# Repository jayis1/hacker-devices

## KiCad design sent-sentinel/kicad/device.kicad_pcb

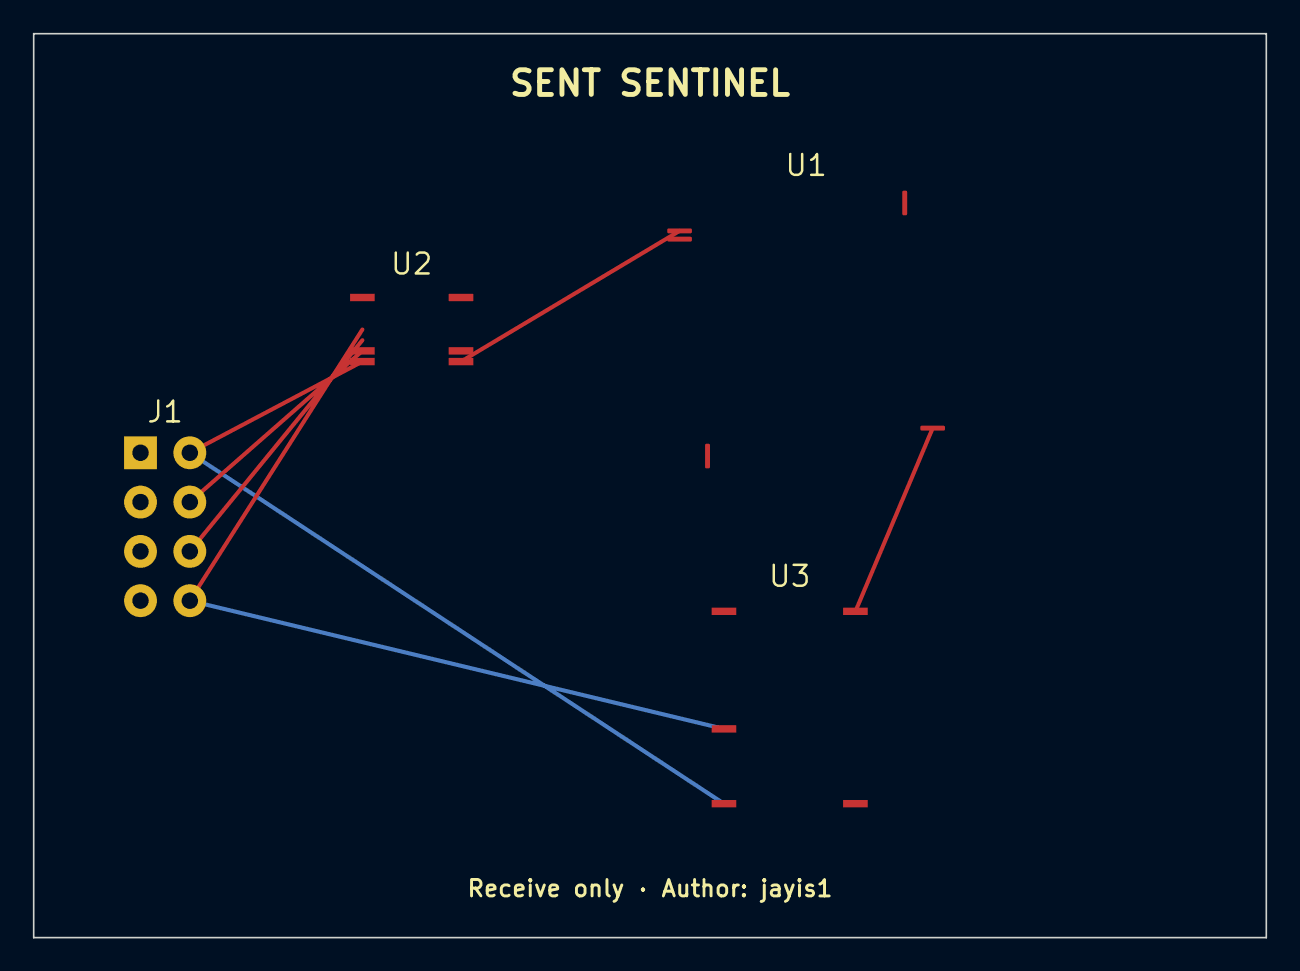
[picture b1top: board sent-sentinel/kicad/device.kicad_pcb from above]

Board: 2 copper layers, 75.0 x 55.0 mm, 4 parts (0 on the bottom side), 7 nets.

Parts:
J1: SENT_AND_ANALOG; Molex_Micro-Fit_3.0_43045-0800_2x04_P3.00mm_Horizontal
U1: STM32G474VET6; LQFP-100_14x14mm_P0.5mm
U2: 74LVC14A; TSSOP-14_4.4x5mm_P0.65mm
U3: ADS8684IDBTR; TSSOP-38_6.1x12.5mm_P0.65mm

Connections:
+3V3: U1.100, U2.14, U3.38
ADC_SPI: U1.50, U3.20
ANALOG_CH0: J1.2, U3.1
ANALOG_CH3: J1.8, U3.8
GND: U1.75, U2.7, U3.19
SENT_CH0_RX: J1.1, U1.1, U2.1, U2.2
SENT_CH1_RX: J1.3, U2.3, U2.4

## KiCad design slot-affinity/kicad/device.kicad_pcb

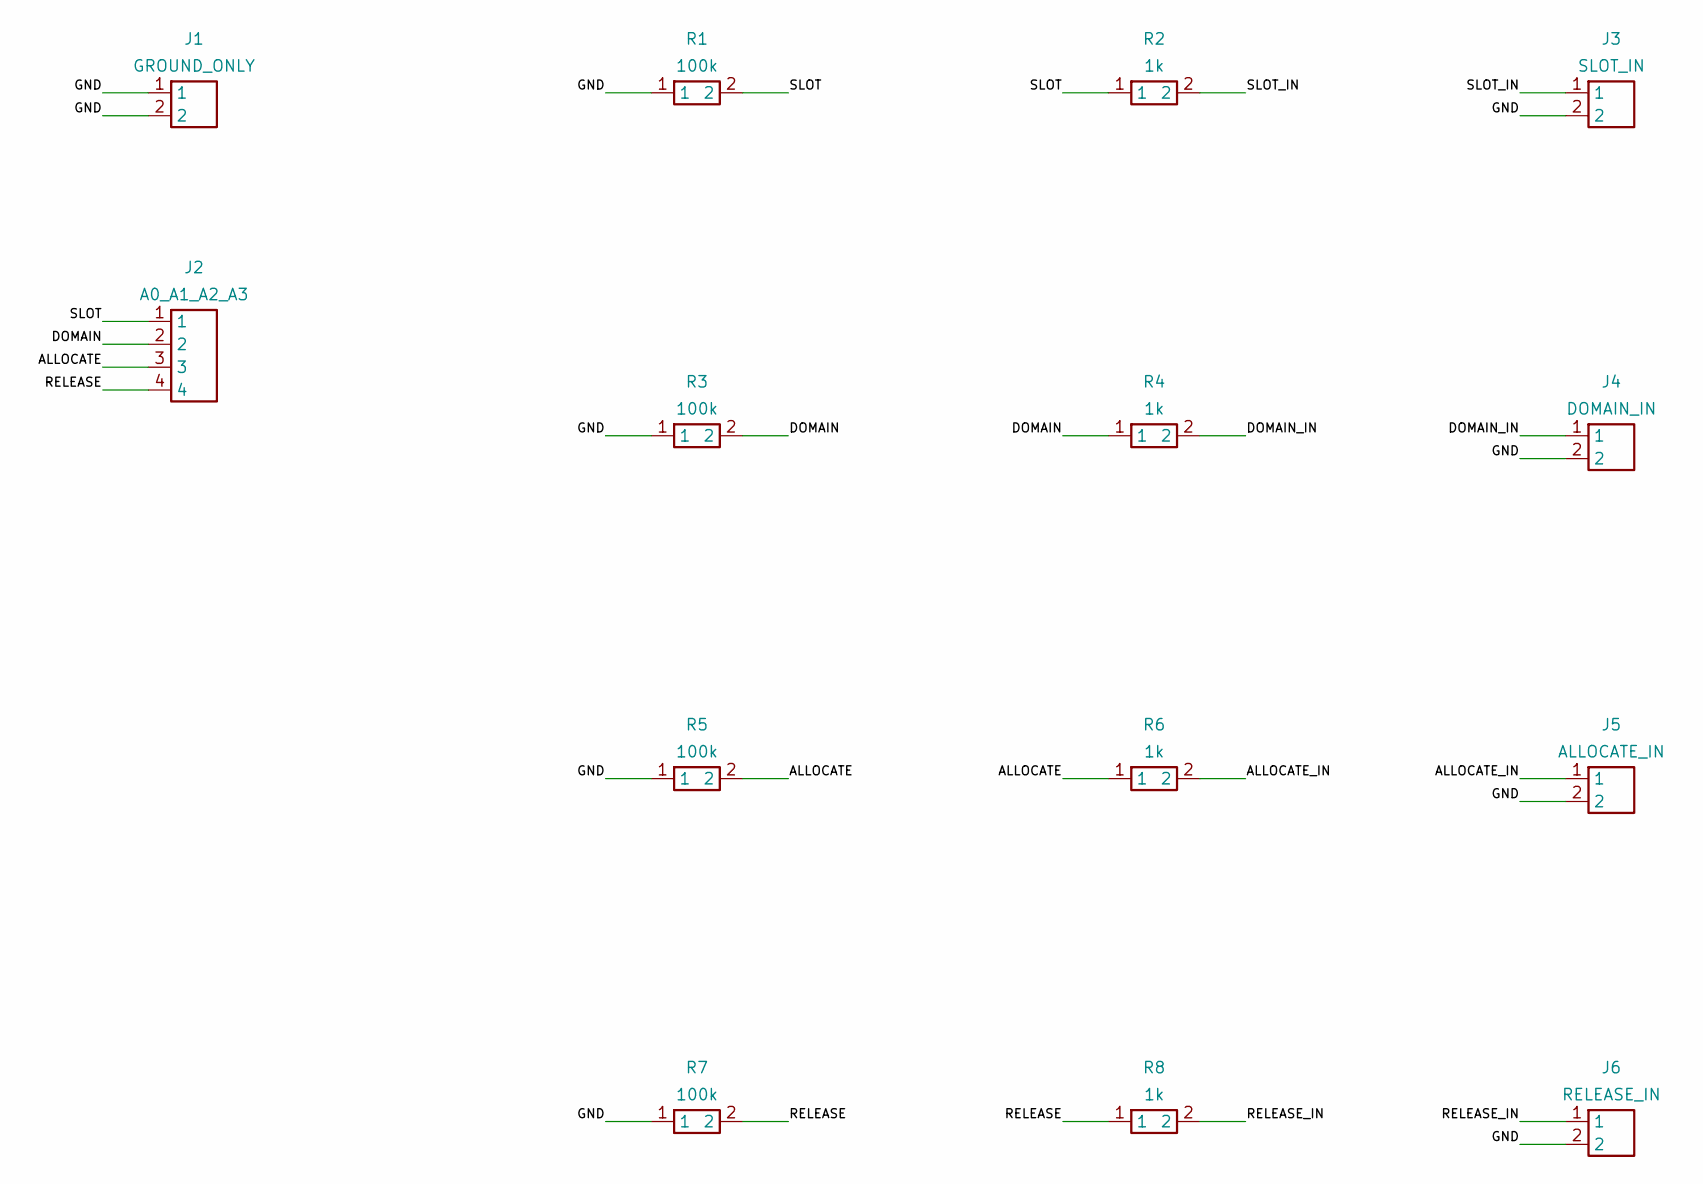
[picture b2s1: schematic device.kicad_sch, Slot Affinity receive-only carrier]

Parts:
J1: GROUND_ONLY; PinHeader_1x02_P2.54mm_Vertical
J2: A0_A1_A2_A3; PinHeader_1x04_P2.54mm_Vertical
J3: SLOT_IN; PinHeader_1x02_P2.54mm_Vertical
J4: DOMAIN_IN; PinHeader_1x02_P2.54mm_Vertical
J5: ALLOCATE_IN; PinHeader_1x02_P2.54mm_Vertical
J6: RELEASE_IN; PinHeader_1x02_P2.54mm_Vertical
R1, R3, R5, R7: 100k; R_Axial_DIN0207_L6.3mm_D2.5mm_P7.62mm_Horizontal
R2, R4, R6, R8: 1k; R_Axial_DIN0207_L6.3mm_D2.5mm_P7.62mm_Horizontal

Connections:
ALLOCATE: J2.3, R5.2, R6.1
ALLOCATE_IN: J5.1, R6.2
DOMAIN: J2.2, R3.2, R4.1
DOMAIN_IN: J4.1, R4.2
GND: J1.1, J1.2, J3.2, J4.2, J5.2, J6.2, R1.1, R3.1, R5.1, R7.1
RELEASE: J2.4, R7.2, R8.1
RELEASE_IN: J6.1, R8.2
SLOT: J2.1, R1.2, R2.1
SLOT_IN: J3.1, R2.2

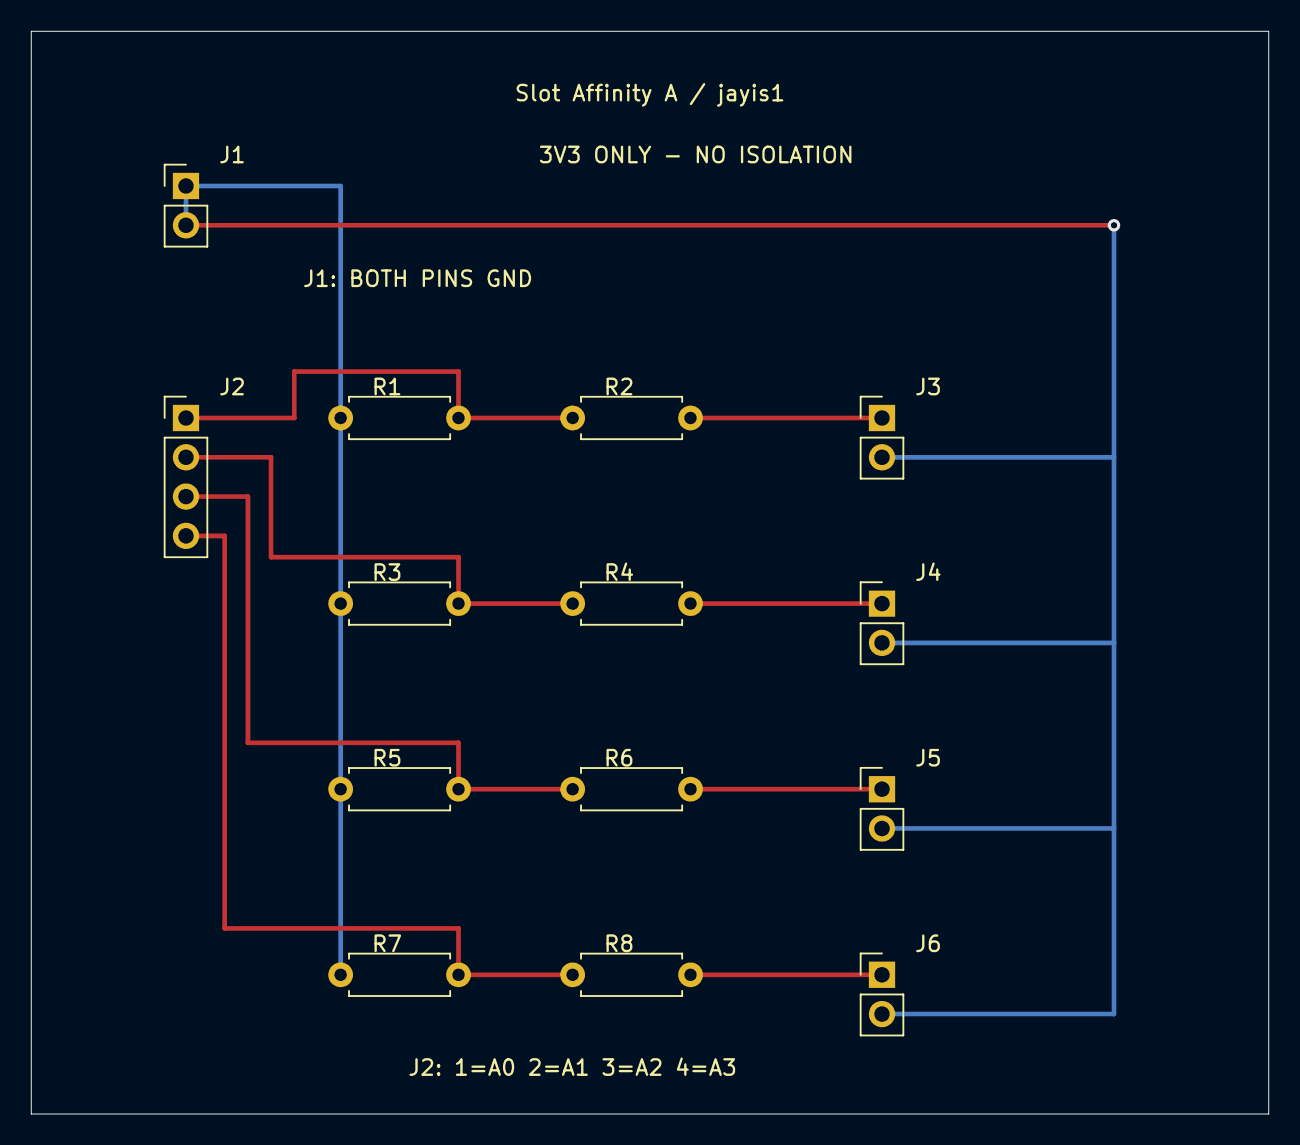
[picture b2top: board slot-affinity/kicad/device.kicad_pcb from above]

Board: 2 copper layers, 80.0 x 70.0 mm, 14 parts (0 on the bottom side), 9 nets.

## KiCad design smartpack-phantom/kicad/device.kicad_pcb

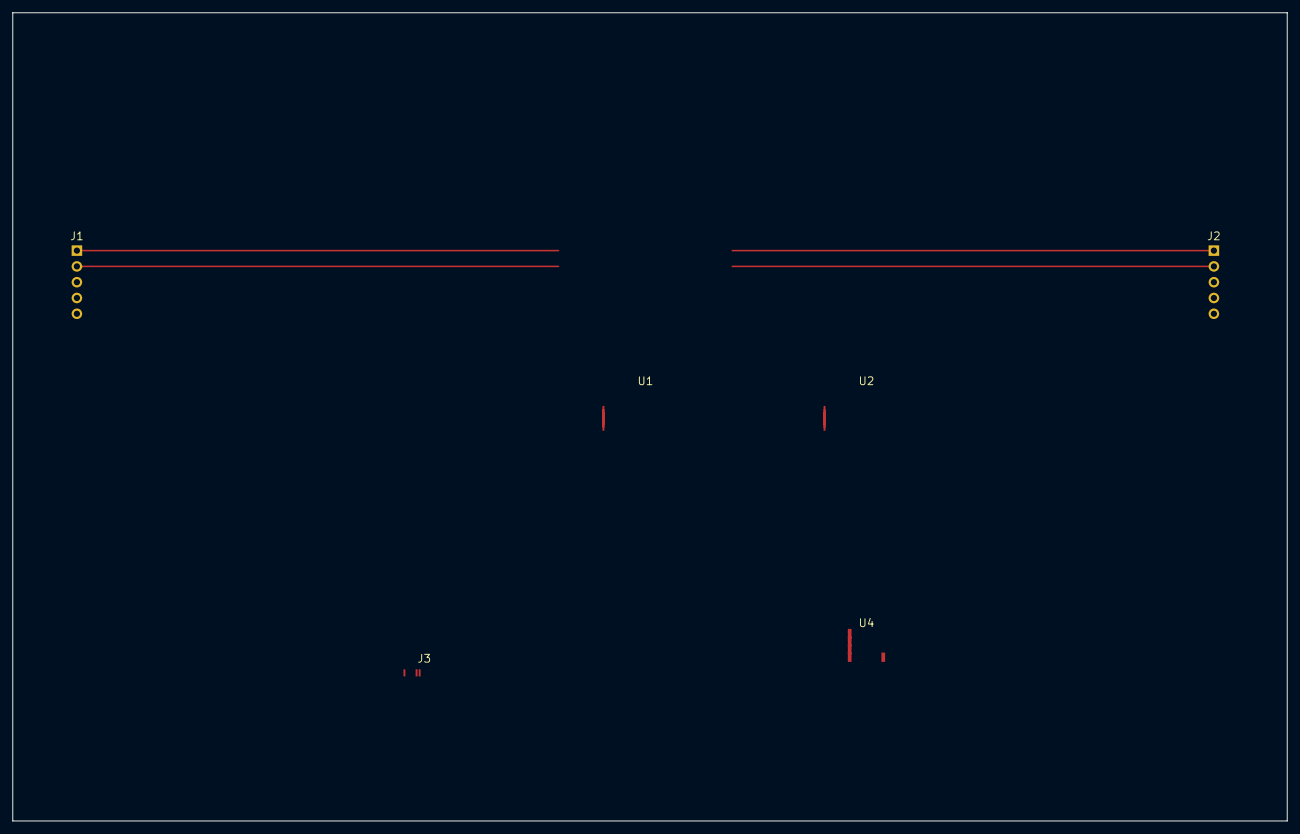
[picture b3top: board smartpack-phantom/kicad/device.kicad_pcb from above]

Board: 2 copper layers, 205.0 x 130.0 mm, 6 parts (0 on the bottom side), 9 nets.

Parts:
J1: HOST_BATTERY_CONN; PinHeader_1x08_P2.54mm_Vertical
J2: PACK_SIDE_CONN; PinHeader_1x08_P2.54mm_Vertical
J3: USB_C_MGMT; USB_C_Receptacle_HRO_TYPE-C-31-M-12
U1: STM32H743VIT6; LQFP-100_14x14mm_P0.5mm
U2: MachXO3LF-4300; TQFP-100_14x14mm_P0.5mm
U4: INA219; SOIC-8_3.9x4.9mm_P1.27mm

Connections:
+3V3: J1.4, U1.5, U2.5, U4.1
ALERT_HOST: J1.3, U2.3
ALERT_PACK: J2.3, U2.4
GND: J1.5, J2.5, J3.A1, U1.6, U2.6, U4.4
PACK_CURRENT_SENSE: J2.4, U4.5
SMBUS_SCL_HOST: J1.1, U1.1, U2.1, U4.2
SMBUS_SCL_PACK: J2.1, U1.3
SMBUS_SDA_HOST: J1.2, U1.2, U2.2, U4.3
SMBUS_SDA_PACK: J2.2, U1.4

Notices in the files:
sideprobe/kicad/device.kicad_sch:
License: CERN-OHL-S v2
Author: jayis1 — CERN-OHL-S v2 hardware, GPL-2.0 firmware
